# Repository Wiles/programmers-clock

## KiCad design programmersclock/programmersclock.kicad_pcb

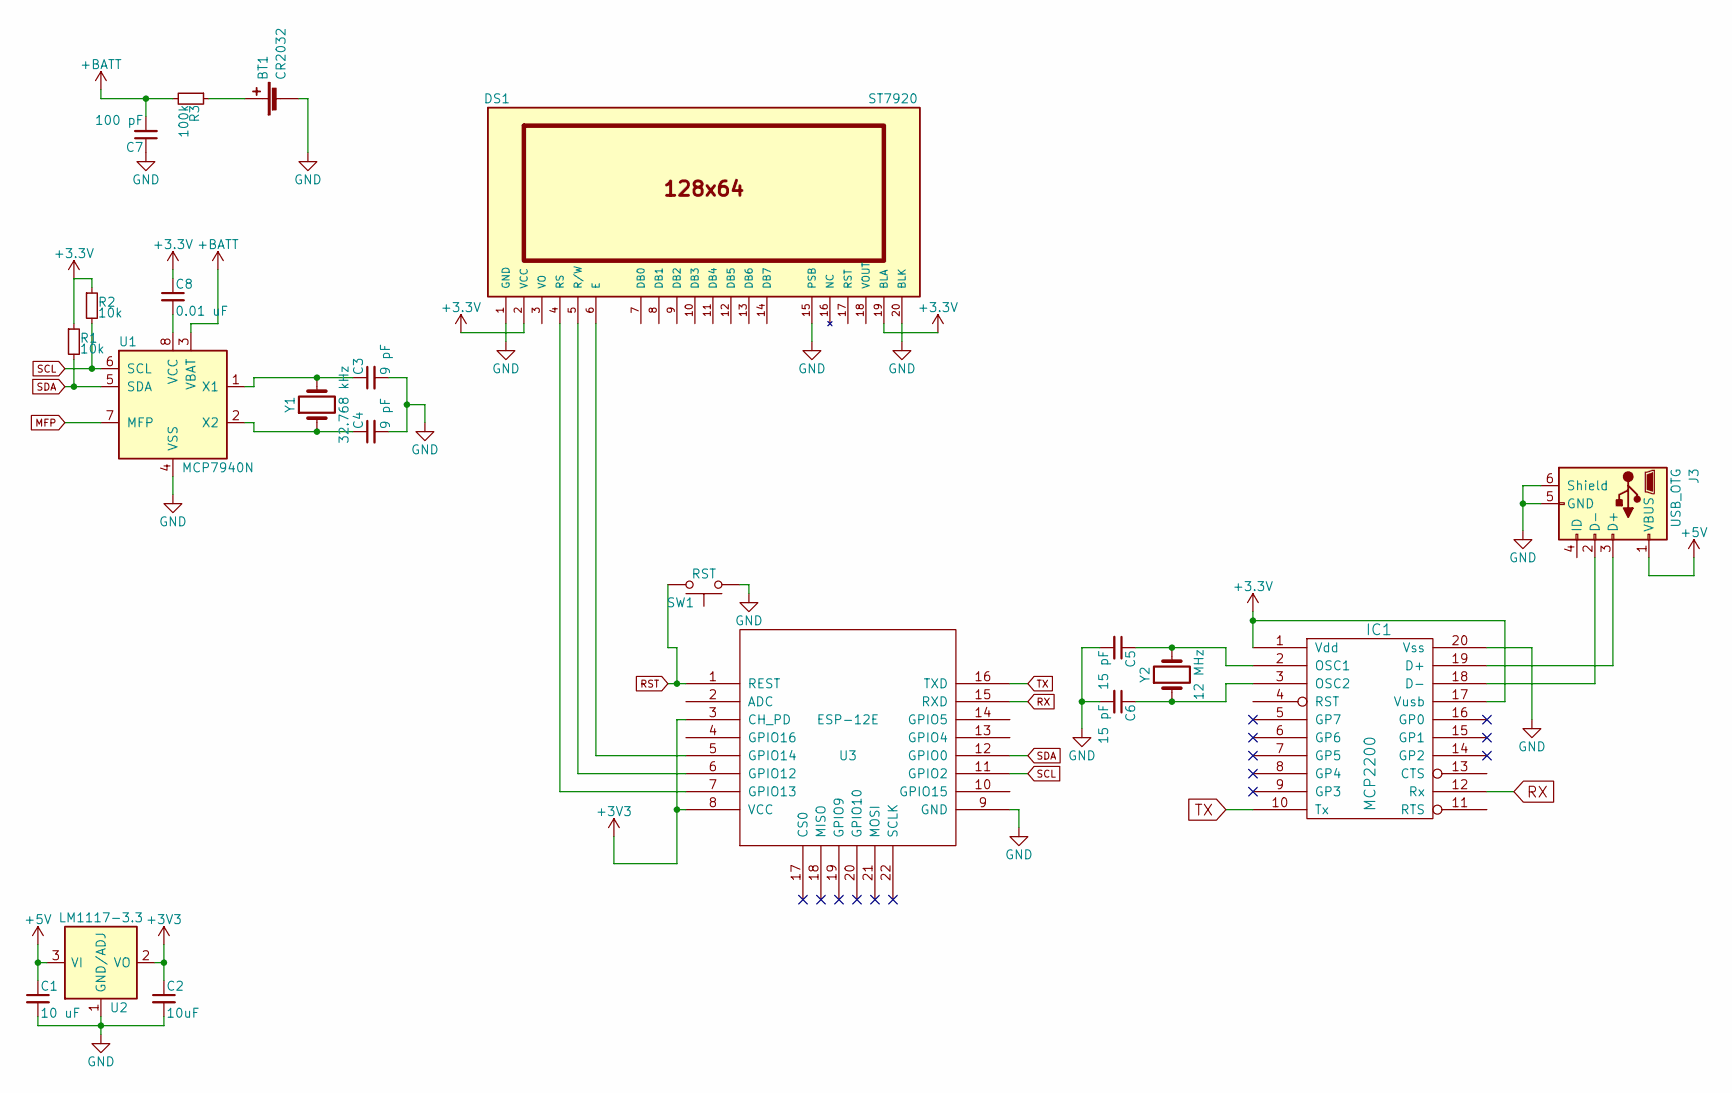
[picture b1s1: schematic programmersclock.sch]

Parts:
BT1: CR2032; Keystone_3034_1x20mm-CoinCell
C1: 10 uF; C_1206
C2: 10uF; C_1206
C3, C4: 9 pF; C_0805
C5, C6: 15 pF; C_0805
C7: 100 pF; C_0805
C8: 0.01 uF; C_0805
DS1: ST7920; Pin_Header_Straight_1x20_Pitch2.54mm
IC1: MCP2200; SOIC-20W_7.5x12.8mm_Pitch1.27mm
J3: USB_OTG; USB_Micro-B_Vertical_Molex-105133-0001
R1, R2: 10k; R_0805
R3: 100k; R_0805
SW1: RST; SW_SPST_EVQP7C
U1: MCP7940N; SOIC-8_3.9x4.9mm_Pitch1.27mm
U2: LM1117-3.3; SOT-223
U3: ESP-12E; ESP-12E_SMD
Y1: 32.768 kHz; Crystal_SMD_3215-2pin_3.2x1.5mm
Y2: 12 MHz; Crystal_SMD_Abracon_ABM3-2pin_5.0x3.2mm

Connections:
+5V: C1.1, J3.1 (VBUS), U2.3 (VI)
+BATT: C7.2, R3.2, U1.3 (VBAT)
GND: BT1.2 (-), C1.2, C2.2, C3.2, C4.2, C5.2, C6.2, C7.1, DS1.1 (GND), DS1.15 (PSB), DS1.20 (BLK), IC1.20 (Vss), J3.5 (GND), J3.6 (Shield), SW1.1, U1.4 (VSS), U2.1 (GND/ADJ), U3.9 (GND)
MFP: U1.7 (MFP)
unnamed: BT1.1 (+), R3.1
unnamed: C3.1, U1.1 (X1), Y1.2
unnamed: C4.1, U1.2 (X2), Y1.1
unnamed: C5.1, IC1.2 (OSC1), Y2.2
unnamed: C6.1, IC1.3 (OSC2), Y2.1
unnamed: C8.2, U1.8 (VCC)
unnamed: DS1.4 (RS), U3.7 (GPIO13)
unnamed: DS1.5 (R/W), U3.6 (GPIO12)
unnamed: DS1.6 (E), U3.5 (GPIO14)
unnamed: IC1.18 (D-), J3.2 (D-)
unnamed: IC1.19 (D+), J3.3 (D+)
RST: SW1.2, U3.1 (REST)
RX: IC1.12 (Rx), U3.15 (RXD)
SCL: R2.2, U1.6 (SCL), U3.11 (GPIO2)
SDA: R1.2, U1.5 (SDA), U3.12 (GPIO0)
TX: IC1.10 (Tx), U3.16 (TXD)

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
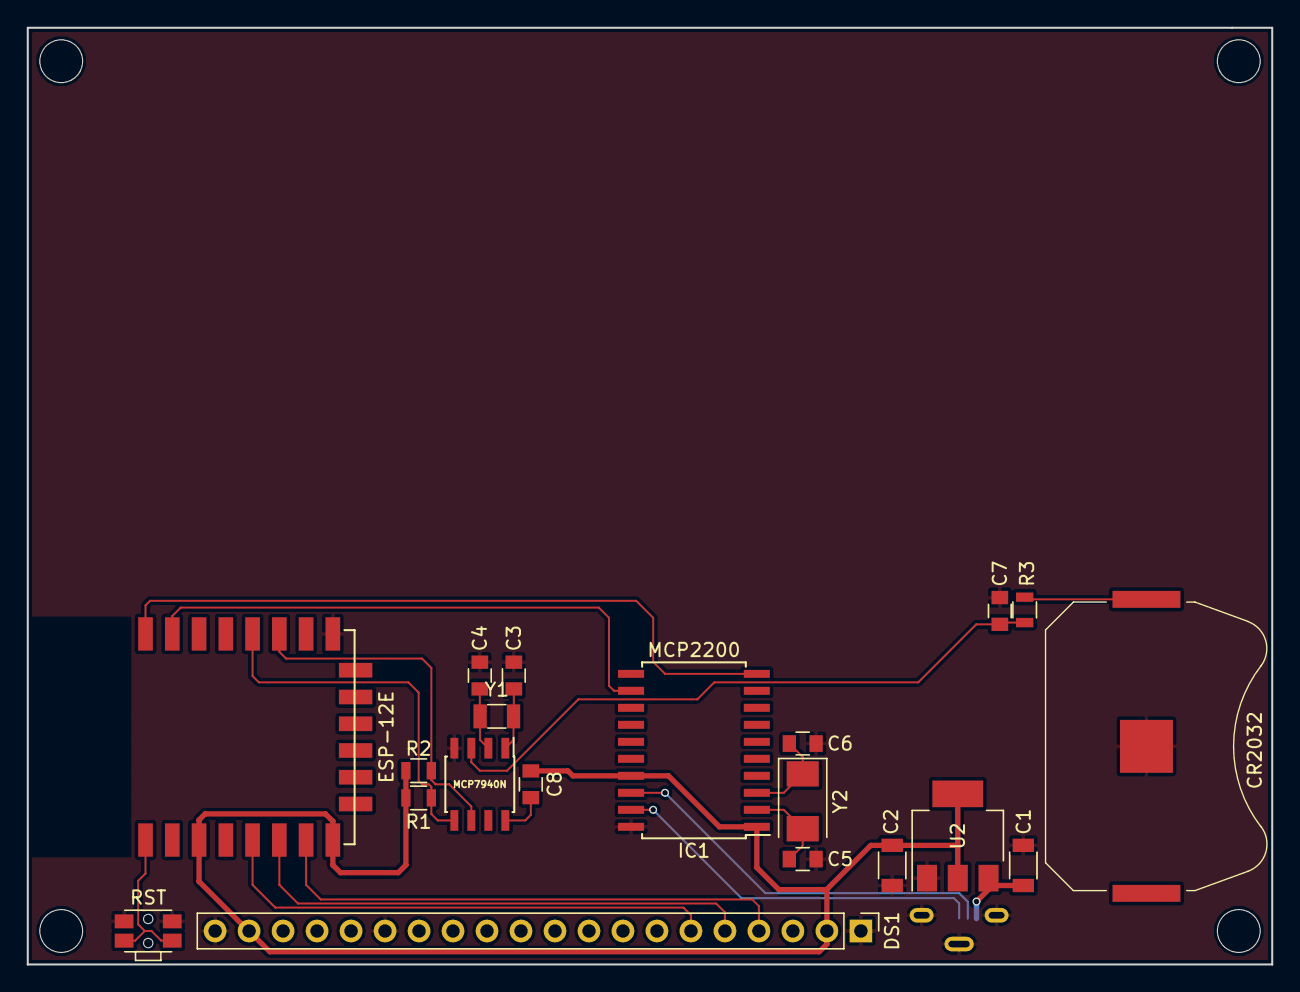
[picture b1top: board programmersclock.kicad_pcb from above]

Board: 2 copper layers, 93.0 x 70.0 mm, 21 parts (1 on the bottom side), 20 nets.

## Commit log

2016-07-30 NTP time lookup
2017-06-29 Start of PCB design
2017-07-01 Create LICENSE
2017-07-01 Added recommended battery circuity for the MCP7940N
2017-07-11 Replaced battery with CR2032 and general layout rework
